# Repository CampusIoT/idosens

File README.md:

# Idosens endpoints :: RIOT boards and applications

[Idosens](https://www.idosens.com/) is a retired product donated to FabMSTIC for research and teaching purposes. The product contains three LoRa endpoints : Base, Sensor and Remote command.

## Getting started

```bash
cd ~/github/RIOT-OS/RIOT
cd examples/hello-world
EXTERNAL_BOARD_DIRS=~/github/campusiot/idosens/boards make BOARD=idosens_sensor
```

## Requirements
* STLink v2 programmer
* FTDI (USB Serial adapter)
* [Tag-Connect 10-pin no-legs probe](https://www.tag-connect.com/product/tc2050-idc-nl-10-pin-no-legs-cable-with-ribbon-connector).
* Optional : [PCB for connecting the Tag-Connect probe to the STLink v2 programmer and the USB Serial adapter](./tagconnect_adapter)

## TODO
* Add a module for TFT fonts

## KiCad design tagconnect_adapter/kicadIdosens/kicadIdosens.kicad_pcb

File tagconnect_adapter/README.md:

# Tag Connect adapter for STLink V2 and FTDI

[Kicad 6](https://www.kicad.org/) project for [Tag-Connect 10-pin no-legs probe](https://www.tag-connect.com/product/tc2050-idc-nl-10-pin-no-legs-cable-with-ribbon-connector).

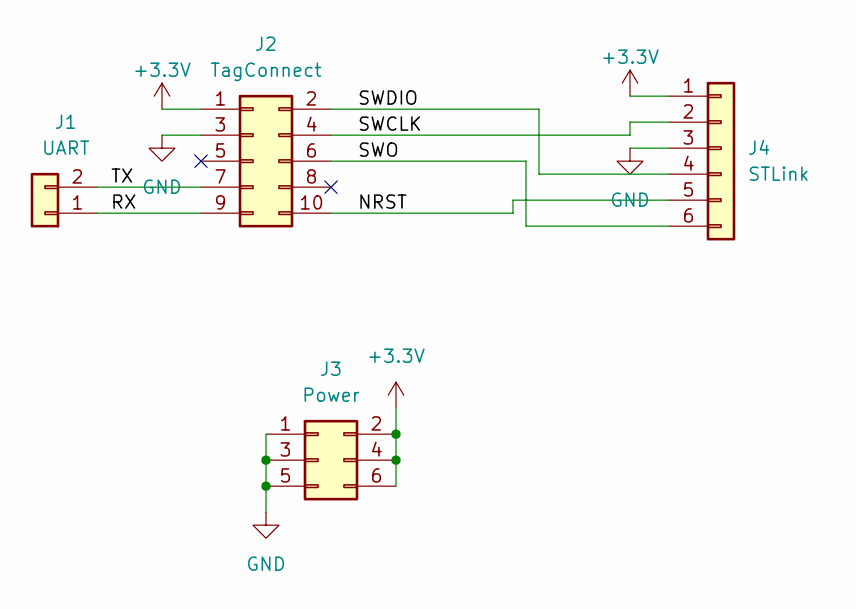
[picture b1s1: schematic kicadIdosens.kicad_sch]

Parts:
J1: UART; PinHeader_1x02_P2.54mm_Vertical
J2: TagConnect; PinHeader_2x05_P2.54mm_Vertical
J3: Power; PinHeader_2x03_P2.54mm_Vertical
J4: STLink; PinHeader_1x06_P2.54mm_Vertical

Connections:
+3V3: J2.1, J3.2, J3.4, J3.6, J4.1
/NRST: J2.10, J4.5
/RX: J1.1, J2.9
/SWCLK: J2.4, J4.2
/SWDIO: J2.2, J4.4
/SWO: J2.6, J4.6
/TX: J1.2, J2.7
GND: J2.3, J3.1, J3.3, J3.5, J4.3

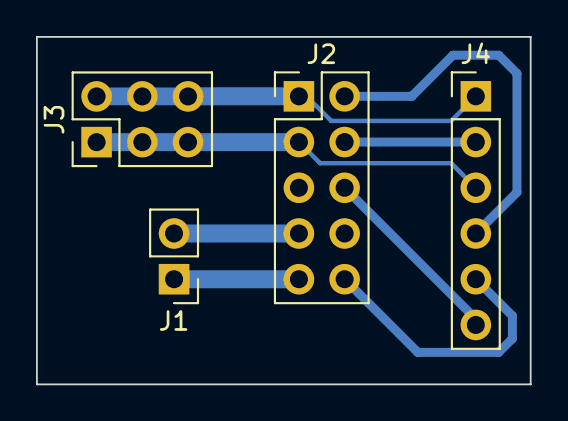
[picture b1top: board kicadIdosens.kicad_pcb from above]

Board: 2 copper layers, 27.4 x 19.3 mm, 4 parts (0 on the bottom side), 8 nets.

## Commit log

2022-05-16 add external boards for RIOT
2022-05-16 add readme
2022-05-16 add contributors
2022-05-16 add dir for docs
2022-05-16 add dir for external modules (drivers ...)
2022-05-16 add dir for applications
2022-05-16 add gitignore
2022-05-16 add application for idosens
2022-05-16 add readme for boards
2022-05-16 add contributor
2022-05-17 improve main; add todos
2022-05-17 add todos
2022-05-17 add idosens image
2022-05-17 move images
2022-05-30 fix space after DEVEUI and APPKEY
2022-05-30 improve todos
2022-05-30 add ref
2022-05-31 initial import from https://github.com/fabMSTICLig/ido-horaires
2022-05-31 add section for images
2022-05-31 init module for e-paper display
2022-05-31 init dir for he tag connect adapter
2022-05-31 add section for requirements
2022-05-31 add EXTERNAL_BOARD_DIRS into Makefile
2022-05-31 add ref to epd_driver
2022-05-31 move bitmap files into bitmap/
2022-05-31 add instruction for using the remote command as a LoRaWAN modem
2022-05-31 fix title
2022-05-31 add uids and key generation
2022-05-31 ajout projet Kicad de l'adaptateur
2022-05-31 WIP: move files to modules/epd_driver
2022-05-31 add refs
2022-05-31 fix refs
2022-06-04 fix path for external modules
2022-06-04 split draw functions from main.c
2022-06-04 check todo
2022-06-08 add readme for field_test_device
2022-08-30 add direct ref
2022-08-30 fix ref
2022-09-15 init dir for 2 new apps
2022-09-15 add todo in clock app
2022-09-15 add fonts dir
2022-09-15 rename font
2022-09-15 add more fonts
2022-09-15 add todo
2022-09-15 fix include
2022-09-15 init dir for nextbus app
2022-09-15 update gitignore
2022-09-15 improve naming
2022-10-01 add geo url when gps
2022-11-26 add annotated image
2022-11-26 add annotated image in readme
2022-11-26 fix path
2022-11-26 change image
2022-12-08 change font
2023-01-04 add qrcode example
2023-01-04 add include
2023-01-11 add snippet
2023-01-11 change key
2023-01-13 add tio
